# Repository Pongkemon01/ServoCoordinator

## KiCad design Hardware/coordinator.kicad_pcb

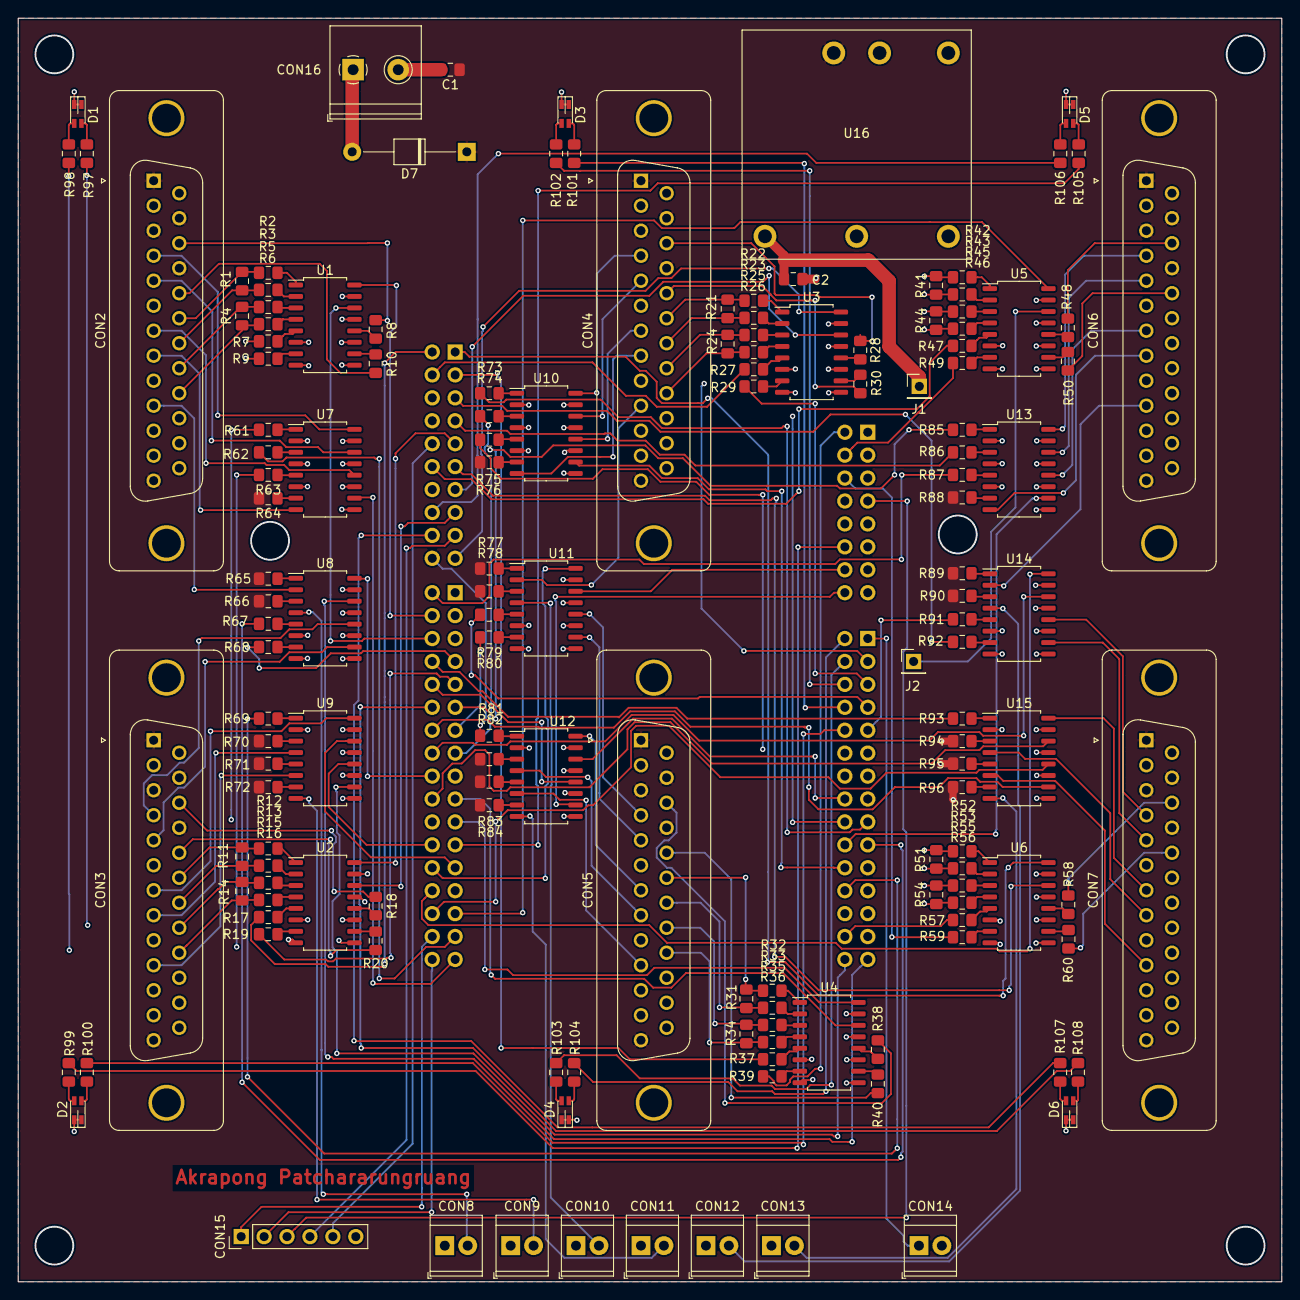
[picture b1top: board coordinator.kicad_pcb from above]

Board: 4 copper layers, 140.0 x 140.0 mm, 151 parts (1 on the bottom side), 251 nets.

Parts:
C1, C2: 10uF 25V; C_0805_2012Metric_Pad1.15x1.40mm_HandSolder
CON1: Nucleo-144-zio
CON2, CON3, CON4, CON5, CON6, CON7: DB25 Main Motor Signal; DSUB-25_Female_Vertical_P2.77x2.84mm_MountingHoles
CON8, CON9, CON10, CON11, CON12, CON13: Home Sensor; TerminalBlock_TE_282834-2_1x02_P2.54mm_Horizontal
CON14: Emergency Stop; TerminalBlock_TE_282834-2_1x02_P2.54mm_Horizontal
CON15: Expansion; PinHeader_1x06_P2.54mm_Vertical
CON16: +24V Power in; TerminalBlock_Philmore_TB132_1x02_P5.00mm_Horizontal
D1, D2, D3, D4, D5, D6: LED_Dual_CACA; LED-Inlux-IN-S85DATRG
D7: 1N4001; D_T-1_P12.70mm_Horizontal
J1: E5V; PinHeader_1x01_P2.54mm_Vertical
J2: PA1; PinHeader_1x01_P2.54mm_Vertical
R1, R11, R21, R31, R41, R51: 680; R_0805_2012Metric_Pad1.15x1.40mm_HandSolder
R2, R3, R5, R6, R7, R9, R12, R13, R15, R16, R17, R19, R22, R23, R25, R26, R27, R29, R32, R33, R35, R36, R37, R39, R42, R43, R45, R46, R47, R49, R52, R53, R55, R56, R57, R59, R61, R62, R63, R67, R68, R69, R73, R74, R75, R79, R80, R81, R85, R86, R87, R91, R92, R93, R97, R98, R99, R100, R101, R102, R103, R104, R105, R106, R107, R108: 330; R_0805_2012Metric_Pad1.15x1.40mm_HandSolder
R4, R14, R24, R34, R44, R54: 120; R_0805_2012Metric_Pad1.15x1.40mm_HandSolder
R8, R10, R18, R20, R28, R30, R38, R40, R48, R50, R58, R60: 3.6k; R_0805_2012Metric_Pad1.15x1.40mm_HandSolder
R64, R65, R66, R70, R71, R72, R76, R77, R78, R82, R83, R84, R88, R89, R90, R94, R95, R96: 4.7K; R_0805_2012Metric_Pad1.15x1.40mm_HandSolder
U1, U2, U3, U4, U5, U6, U7, U8, U9, U10, U11, U12, U13, U14, U15: TLP292-4; SOIC-16_4.55x10.3mm_P1.27mm
U16: PDQE10

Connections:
+3V3: CON1.8-7, CON15.3
+5V: C2.1, J1.1, U16.3
+24V: C1.1, CON2.1, CON2.3, CON2.13, CON2.15, CON2.17, CON3.1, CON3.3, CON3.13, CON3.15, CON3.17, CON4.1, CON4.3, CON4.13, CON4.15, CON4.17, CON5.1, CON5.3, CON5.13, CON5.15, CON5.17, CON6.1, CON6.3, CON6.13, CON6.15, CON6.17, CON7.1, CON7.3, CON7.13, CON7.15, CON7.17, D7.1, R64.2, R65.2, R66.2, R70.2, R71.2, R72.2, R76.2, R77.2, R78.2, R82.2, R83.2, R84.2, R88.2, R89.2, R90.2, R94.2, R95.2, R96.2, U16.2
EMERGENCY_N: CON1.9-1, CON14.1
EXT_INT1: CON1.7-17, CON15.4
EXT_INT2: CON1.7-10, CON15.5
GND: C2.2, CON1.7-8, CON1.8-11, CON1.8-13, CON1.9-12, CON1.9-23, CON1.10-3, CON1.10-5, CON1.10-17, CON1.10-22, CON1.10-27, CON14.2, CON15.6, D1.1, D1.3, D2.1, D2.3, D3.1, D3.3, D4.1, D4.3, D5.1, D5.3, D6.1, D6.3, U1.6, U1.8, U1.13, U1.15, U2.6, U2.8, U2.13, U2.15, U3.6, U3.8, U3.13, U3.15, U4.6, U4.8, U4.13, U4.15, U5.6, U5.8, U5.13, U5.15, U6.6, U6.8, U6.13, U6.15, U7.2, U7.4, U7.6, U7.9, U8.6, U8.8, U8.13, U8.15, U9.2, U9.9, U9.11, U9.13, U10.2, U10.4, U10.6, U10.9, U11.6, U11.8, U11.13, U11.15, U12.2, U12.9, U12.11, U12.13, U13.2, U13.4, U13.6, U13.9, U14.6, U14.8, U14.13, U14.15, U15.2, U15.9, U15.11, U15.13, U16.5
GNDPWR: C1.2, CON2.0, CON2.2, CON2.9, CON2.11, CON2.12, CON3.0, CON3.2, CON3.9, CON3.11, CON3.12, CON4.0, CON4.2, CON4.9, CON4.11, CON4.12, CON5.0, CON5.2, CON5.9, CON5.11, CON5.12, CON6.0, CON6.2, CON6.9, CON6.11, CON6.12, CON7.0, CON7.2, CON7.9, CON7.11, CON7.12, CON8.1, CON9.1, CON10.1, CON11.1, CON12.1, CON13.1, CON16.2, U1.9, U1.11, U2.9, U2.11, U3.9, U3.11, U4.9, U4.11, U5.9, U5.11, U6.9, U6.11, U7.11, U7.13, U7.15, U8.9, U8.11, U9.15, U10.11, U10.13, U10.15, U11.9, U11.11, U12.15, U13.11, U13.13, U13.15, U14.9, U14.11, U15.15, U16.1
I2C_SCL: CON1.10-32, CON15.1
I2C_SDA: CON1.10-34, CON15.2
M1_ALARM_EXT: CON2.8, U7.8
M1_ALARM_N: CON1.10-33, U7.10
M1_ALRM_RES: CON1.10-31, R62.2
M1_ALRM_RES_EXT: CON2.5, U7.14
M1_COMPLETE_EXT: CON2.10, U8.2
M1_COMPLETE_N: CON1.10-18, U8.16
M1_DEV_CLR: CON1.9-26, R63.2
M1_DEV_CLR_EXT: CON2.7, U7.12
M1_DIR: CON1.9-3, R9.1
M1_DIR_N: CON2.18, R10.2
M1_ENCA: CON1.10-4, U1.16
M1_ENCB: CON1.10-6, U1.14
M1_HOME_EXT: CON8.2, U8.4
M1_HOME_N: CON1.9-29, U8.14
M1_OUTA_N: CON2.20, R1.2, R3.1
M1_OUTA_P: CON2.19, R1.1, R2.1
M1_OUTB_N: CON2.22, R4.2, R6.1
M1_OUTB_P: CON2.21, R4.1, R5.1
M1_PULSE: CON1.9-18, R7.1
M1_PULSE_N: CON2.16, R8.2
M1_SRV_ON: CON1.9-21, R61.2
M1_SRV_ON_EXT: CON2.4, U7.16
M2_ALARM_EXT: CON3.8, U9.4
M2_ALARM_N: CON1.10-25, U9.14
M2_ALRM_RES: CON1.10-7, R68.2
M2_ALRM_RES_EXT: CON3.5, U8.10
M2_COMPLETE_EXT: CON3.10, U9.6
M2_COMPLETE_N: CON1.10-24, U9.12
M2_DEV_CLR: CON1.9-24, R69.2
M2_DEV_CLR_EXT: CON3.7, U9.16
M2_DIR: CON1.10-9, R19.1
M2_DIR_N: CON3.18, R20.2
M2_ENCA: CON1.7-9, U2.16
M2_ENCB: CON1.7-15, U2.14
M2_HOME_EXT: CON9.2, U9.8
M2_HOME_N: CON1.9-30, U9.10
M2_OUTA_N: CON3.20, R11.2, R13.1
M2_OUTA_P: CON3.19, R11.1, R12.1
M2_OUTB_N: CON3.22, R14.2, R16.1
M2_OUTB_P: CON3.21, R14.1, R15.1
M2_PULSE: CON1.7-2, R17.1
M2_PULSE_N: CON3.16, R18.2
M2_SRV_ON: CON1.9-19, R67.2
M2_SRV_ON_EXT: CON3.4, U8.12
M3_ALARM_EXT: CON4.8, U10.8
M3_ALARM_N: CON1.9-22, U10.10
M3_ALRM_RES: CON1.10-15, R74.2
M3_ALRM_RES_EXT: CON4.5, U10.14
M3_COMPLETE_EXT: CON4.10, U11.2
M3_COMPLETE_N: CON1.10-26, U11.16
M3_DEV_CLR: CON1.9-11, R75.2
M3_DEV_CLR_EXT: CON4.7, U10.12
M3_DIR: CON1.9-5, R29.1
M3_DIR_N: CON4.18, R30.2
M3_ENCA: CON1.7-19, U3.16
M3_ENCB: CON1.7-13, U3.14
M3_HOME_EXT: CON10.2, U11.4
M3_HOME_N: CON1.8-14, U11.14
M3_OUTA_N: CON4.20, R21.2, R23.1
M3_OUTA_P: CON4.19, R21.1, R22.1
M3_OUTB_N: CON4.22, R24.2, R26.1
M3_OUTB_P: CON4.21, R24.1, R25.1
M3_PULSE: CON1.7-4, R27.1
M3_PULSE_N: CON4.16, R28.2
M3_SRV_ON: CON1.9-17, R73.2
M3_SRV_ON_EXT: CON4.4, U10.16
M4_ALARM_EXT: CON5.8, U12.4
M4_ALARM_N: CON1.9-16, U12.14
M4_ALRM_RES: CON1.10-13, R80.2
M4_ALRM_RES_EXT: CON5.5, U11.10
M4_COMPLETE_EXT: CON5.10, U12.6
M4_COMPLETE_N: CON1.10-10, U12.12
M4_DEV_CLR: CON1.7-20, R81.2
M4_DEV_CLR_EXT: CON5.7, U12.16
M4_DIR: CON1.8-2, R39.1
M4_DIR_N: CON5.18, R40.2
M4_ENCA: CON1.10-21, U4.16
M4_ENCB: CON1.10-19, U4.14
M4_HOME_EXT: CON11.2, U12.8
M4_HOME_N: CON1.8-16, U12.10
M4_OUTA_N: CON5.20, R31.2, R33.1
M4_OUTA_P: CON5.19, R31.1, R32.1
M4_OUTB_N: CON5.22, R34.2, R36.1
M4_OUTB_P: CON5.21, R34.1, R35.1
M4_PULSE: CON1.7-3, R37.1
M4_PULSE_N: CON5.16, R38.2
M4_SRV_ON: CON1.9-7, R79.2
M4_SRV_ON_EXT: CON5.4, U11.12
M5_ALARM_EXT: CON6.8, U13.8
M5_ALARM_N: CON1.9-20, U13.10
M5_ALRM_RES: CON1.7-7, R86.2
M5_ALRM_RES_EXT: CON6.5, U13.14
M5_COMPLETE_EXT: CON6.10, U14.2
M5_COMPLETE_N: CON1.10-28, U14.16
M5_DEV_CLR: CON1.10-2, R87.2
M5_DEV_CLR_EXT: CON6.7, U13.12
M5_DIR: CON1.8-4, R49.1
M5_DIR_N: CON6.18, R50.2
M5_ENCA: CON1.10-29, U5.16
M5_ENCB: J2.1, U5.14
M5_HOME_EXT: CON12.2, U14.4
M5_HOME_N: CON1.10-16, U14.14
M5_OUTA_N: CON6.20, R41.2, R43.1
M5_OUTA_P: CON6.19, R41.1, R42.1
M5_OUTB_N: CON6.22, R44.2, R46.1
M5_OUTB_P: CON6.21, R44.1, R45.1
M5_PULSE: CON1.7-12, R47.1
M5_PULSE_N: CON6.16, R48.2
M5_SRV_ON: CON1.10-11, R85.2
M5_SRV_ON_EXT: CON6.4, U13.16
M6_ALARM_EXT: CON7.8, U15.4
M6_ALARM_N: CON1.10-20, U15.14
M6_ALRM_RES: CON1.7-5, R92.2
M6_ALRM_RES_EXT: CON7.5, U14.10
M6_COMPLETE_EXT: CON7.10, U15.6
M6_COMPLETE_N: CON1.10-30, U15.12
M6_DEV_CLR: CON1.10-8, R93.2
M6_DEV_CLR_EXT: CON7.7, U15.16
M6_DIR: CON1.8-6, R59.1
M6_DIR_N: CON7.18, R60.2
M6_ENCA: CON1.7-1, U6.16
M6_ENCB: CON1.7-11, U6.14
M6_HOME_EXT: CON13.2, U15.8
M6_HOME_N: CON1.10-14, U15.10
M6_OUTA_N: CON7.20, R51.2, R53.1
M6_OUTA_P: CON7.19, R51.1, R52.1
M6_OUTB_N: CON7.22, R54.2, R56.1
M6_OUTB_P: CON7.21, R54.1, R55.1
M6_PULSE: CON1.9-28, R57.1
M6_PULSE_N: CON7.16, R58.2
M6_SRV_ON: CON1.9-9, R91.2
M6_SRV_ON_EXT: CON7.4, U14.12
unnamed: CON1.7-16, R106.1
unnamed: CON1.7-18, R107.1
unnamed: CON1.8-12, R99.1
unnamed: CON1.9-2, R104.1
unnamed: CON1.9-4, R103.1
unnamed: CON1.9-6, R102.1
unnamed: CON1.9-8, R101.1
unnamed: CON1.9-10, R100.1
unnamed: CON1.9-25, R97.1
unnamed: CON1.9-27, R98.1
unnamed: CON1.10-12, R108.1
unnamed: CON1.10-23, R105.1
unnamed: CON16.1, D7.2
unnamed: D1.2, R97.2
unnamed: D1.4, R98.2
unnamed: D2.2, R99.2
unnamed: D2.4, R100.2
unnamed: D3.2, R101.2
unnamed: D3.4, R102.2
unnamed: D4.2, R103.2
unnamed: D4.4, R104.2
unnamed: D5.2, R105.2
unnamed: D5.4, R106.2
unnamed: D6.2, R107.2
unnamed: D6.4, R108.2
unnamed: R2.2, U1.1
unnamed: R3.2, U1.2
unnamed: R5.2, U1.3
unnamed: R6.2, U1.4
unnamed: R7.2, U1.5
unnamed: R8.1, U1.12
unnamed: R9.2, U1.7
unnamed: R10.1, U1.10
unnamed: R12.2, U2.1
unnamed: R13.2, U2.2
unnamed: R15.2, U2.3
unnamed: R16.2, U2.4
unnamed: R17.2, U2.5
unnamed: R18.1, U2.12
unnamed: R19.2, U2.7
unnamed: R20.1, U2.10
unnamed: R22.2, U3.1
unnamed: R23.2, U3.2
unnamed: R25.2, U3.3
unnamed: R26.2, U3.4
unnamed: R27.2, U3.5
unnamed: R28.1, U3.12
unnamed: R29.2, U3.7
unnamed: R30.1, U3.10
unnamed: R32.2, U4.1
unnamed: R33.2, U4.2
unnamed: R35.2, U4.3
unnamed: R36.2, U4.4
unnamed: R37.2, U4.5
unnamed: R38.1, U4.12
unnamed: R39.2, U4.7
unnamed: R40.1, U4.10
unnamed: R42.2, U5.1
unnamed: R43.2, U5.2
unnamed: R45.2, U5.3
unnamed: R46.2, U5.4
unnamed: R47.2, U5.5
unnamed: R48.1, U5.12
unnamed: R49.2, U5.7
unnamed: R50.1, U5.10
unnamed: R52.2, U6.1
unnamed: R53.2, U6.2
unnamed: R55.2, U6.3
unnamed: R56.2, U6.4
unnamed: R57.2, U6.5
unnamed: R58.1, U6.12
unnamed: R59.2, U6.7
unnamed: R60.1, U6.10
unnamed: R61.1, U7.1
unnamed: R62.1, U7.3
unnamed: R63.1, U7.5
unnamed: R64.1, U7.7
unnamed: R65.1, U8.1
unnamed: R66.1, U8.3
unnamed: R67.1, U8.5
unnamed: R68.1, U8.7
unnamed: R69.1, U9.1
unnamed: R70.1, U9.3
unnamed: R71.1, U9.5
unnamed: R72.1, U9.7
unnamed: R73.1, U10.1
unnamed: R74.1, U10.3
unnamed: R75.1, U10.5
unnamed: R76.1, U10.7
unnamed: R77.1, U11.1
unnamed: R78.1, U11.3
unnamed: R79.1, U11.5
unnamed: R80.1, U11.7
unnamed: R81.1, U12.1
unnamed: R82.1, U12.3
unnamed: R83.1, U12.5
unnamed: R84.1, U12.7
unnamed: R85.1, U13.1
unnamed: R86.1, U13.3
unnamed: R87.1, U13.5
unnamed: R88.1, U13.7
unnamed: R89.1, U14.1
unnamed: R90.1, U14.3
unnamed: R91.1, U14.5
unnamed: R92.1, U14.7
unnamed: R93.1, U15.1
unnamed: R94.1, U15.3
unnamed: R95.1, U15.5
unnamed: R96.1, U15.7

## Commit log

2019-07-25 Added README.md, .gitignore (C++) files
2019-07-25 Updated .gitignore
2019-07-25 Initialize the project
2019-07-25 Squashed 'Software/nuttx/' content from commit 933e9e407b
    git-subtree-dir: Software/nuttx
    git-subtree-split: 933e9e407b55cec357d3e7daf558a105d2c7507d
2019-07-25 Squashed 'Software/apps/' content from commit 44a8d7c80e
    git-subtree-dir: Software/apps
    git-subtree-split: 44a8d7c80e1365028186bfafde25bd682f06923b
2019-09-02 First rough driver compilation for PTTEP show
2019-09-02 Squashed 'Software/nuttx/' changes from 933e9e407b..100fe59ff2
    100fe59ff2 net/arp/arp.h: Remove an unused structure definition.
    85770966ff boards/Board.mk: Add support to pass dependency paths. boards/arm/cxd56xx/common/Makefile: Add correct dependency paths for board/ and src/ subdirectories.
    d596e56c3d net/local/local_conn.c: Removed un-ncessary memset(). Connection structure is allocated with kmm_zalloc() which will clear all memory.
    6266e067e9 net/: Re-order the content of all address-family socket 'connection' structures so that they begin with a comomon prologue. This permits better use of logic for different address family ty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
    19e1db3f97 arch/arm/src/stm32/hardware/stm32_ad
2019-09-02 Squashed 'Software/apps/' changes from 44a8d7c80e..104d7f3716
    104d7f3716 Merged in masayuki2009/nuttx.apps/gs2200m_supports_SIOCGIFHWADDR (pull request #199)
    aa6d5106e7 Makefile: Added support for application-specific export target. Used by nuttx/tools/mkexport.sh.
    3a75edca20 Fix minor typo/copy-paste: 'will be use when'->'will be used when'
    ac61c18fcc Move apps/builtins/builtin_forindex.c to nuttx/libs/libc/builtin since it is required by kernel logic as well. Other changes account for movement of builtin.h from nuttx/include/nuttx/binf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
    839efa6669 Merged in david_alessio/apps/bugfix/i2ctool-dev-clobbers-slave-config (pull request #198)
    811086ff85
2019-09-02 Re-organize and re-configure to conform with new Nuttx structure.
2019-09-04 First finish of all drivers. Ready for application layer.
2019-09-04 Expose Timer7 to user-space.
2019-09-04 Clean up all configuration. Make the RAMLOG fully FIFO. Move all initialization steps off the NSH to kernel's late_initilalization.
2019-09-12 First working release
2019-09-17 Add support for MPU9250 (Sparkfun break-out) in I2C mode at 100Hz sensor rate
2019-09-26 Freeze version 1 as the RS-422 interface cannot tolerate noise generated from the driver.
2019-10-02 Original commit of version 2. The firmware is similar to version 1 plus some bug fixes
2019-10-27 Commit before big change in PFM
2019-10-28 Complete driver layer.
2019-11-27 Complete all. Waiting for final debug
2019-11-27 Version 2.0.1. Fixed Home-sensor connection bug
2019-12-03 Finished!!!
2020-02-11 Finalized motor control to compensate drifts
2020-07-03 Change configuration for logging extension - Enable RTC - Enable Syslog buffer (CONFIG_SYSLOG_BUFFER)
2020-08-31 Add logging
2020-09-01 Minor fixed in logging
